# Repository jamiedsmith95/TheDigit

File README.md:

# TheDigit
A chorded keyboard, roughly based on the ginny, the Digit has 5 keys on each side for a total of 10. Inputs not found directly on the keys are accessed with a mixture of layering and chording.

## Firmware
Zephyr Mechanical Keyboards or ZMK is an open source firmware for keyboards. Within ZMK are a number of useful functionalities that make such a keyboard usable.
- Layering
- Chording
- Tap-dance
- Tap-hold
- Macros

### Layers
Layers allow the user to change the function of the keys they have access to as well as the ability to change the chords they have access to. For example, a number layer could change the main 8 keys to the numbers 1 to 8, with 9 and 0 put as an easy to reach chord. Additional layers can then be added for virtually unlimited functionality. Layers can be activated in multiple ways allowing for enhanced customisation.

1. They can be toggled on or off.
2. They can be turned momentarily on, this means that the layer is deactivated if the key or chord is released.
3. They can be turned on while all other layers are deactivated.

### Chords
Chords are triggered by pressing two or more keys down at the same time (within a small tolerance). With the available combinations of two keys the user now has more than enough inputs available for the alphabet and the more common punctuation.

### Tap-dance
Tap dancing is the name given to the keyboard behaviour that allows the user to have a key (or chord) behave differently depending on how many times it is pressed within a short window. For example, pressing shift once could give you shift and twice for CAPSLOCK.

### Tap-hold 
Similarly to tap-dance, tap-hold allows the user to trigger different behaviours when they tap a key and when they hold it. For example, pressing ESC for escape and hold it down to activate a layer.

### Macros
Macros are one of the features that really speed up typing and allow the user to properly customise the firmware. A macro can be configured to input sequences of keys, whether they form words or are combinations of modifiers that trigger a frequently used shortcut. This allows typing words or even frequently used phrases with a single chord. 

## The keymap
The keymap is a file that holds all the information specifying these behaviours. The keymap and other ZMK files I use can be found in zmk_keymap.

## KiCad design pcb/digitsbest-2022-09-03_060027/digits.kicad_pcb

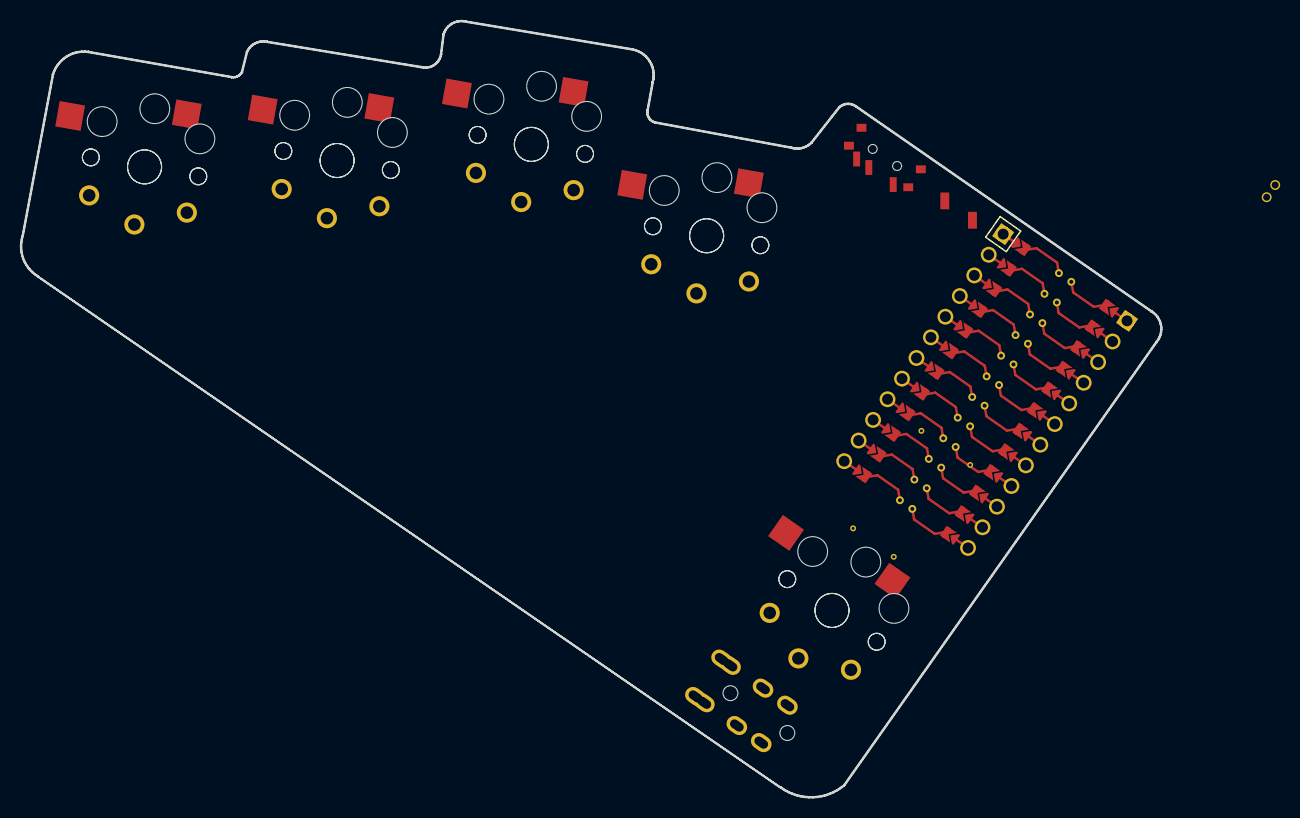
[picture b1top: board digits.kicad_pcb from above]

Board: 2 copper layers, 115.0 x 78.3 mm, 11 parts (0 on the bottom side), 6 nets, no tracks yet.

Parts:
MCU1: ProMicro
S1, S2, S3, S4, S5, S6, S7, S8, S9, S10: PG1350

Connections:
GND: MCU1.2, MCU1.21, MCU1.22, S1.2, S2.2, S3.2, S4.2, S5.2, S6.2, S7.2, S8.2, S9.2, S10.2
P6: MCU1.16, S1.1, S2.1
P7: MCU1.15, S3.1, S4.1
P8: MCU1.14, S5.1, S6.1
P9: MCU1.13, S7.1, S8.1
P10: MCU1.12, S9.1, S10.1

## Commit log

2023-12-03 initial commit.. 3d case file, pcb kicad files, and the keymap for zmk
2023-12-04 add to readme
2023-12-04 readme change
